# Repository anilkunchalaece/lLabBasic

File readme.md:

See the output at : 
http://pamda1ver2.16mb.com/index.html

refrences : 
https://developer.ibm.com/messaging/2013/05/22/program-messaging-apps-javascript/

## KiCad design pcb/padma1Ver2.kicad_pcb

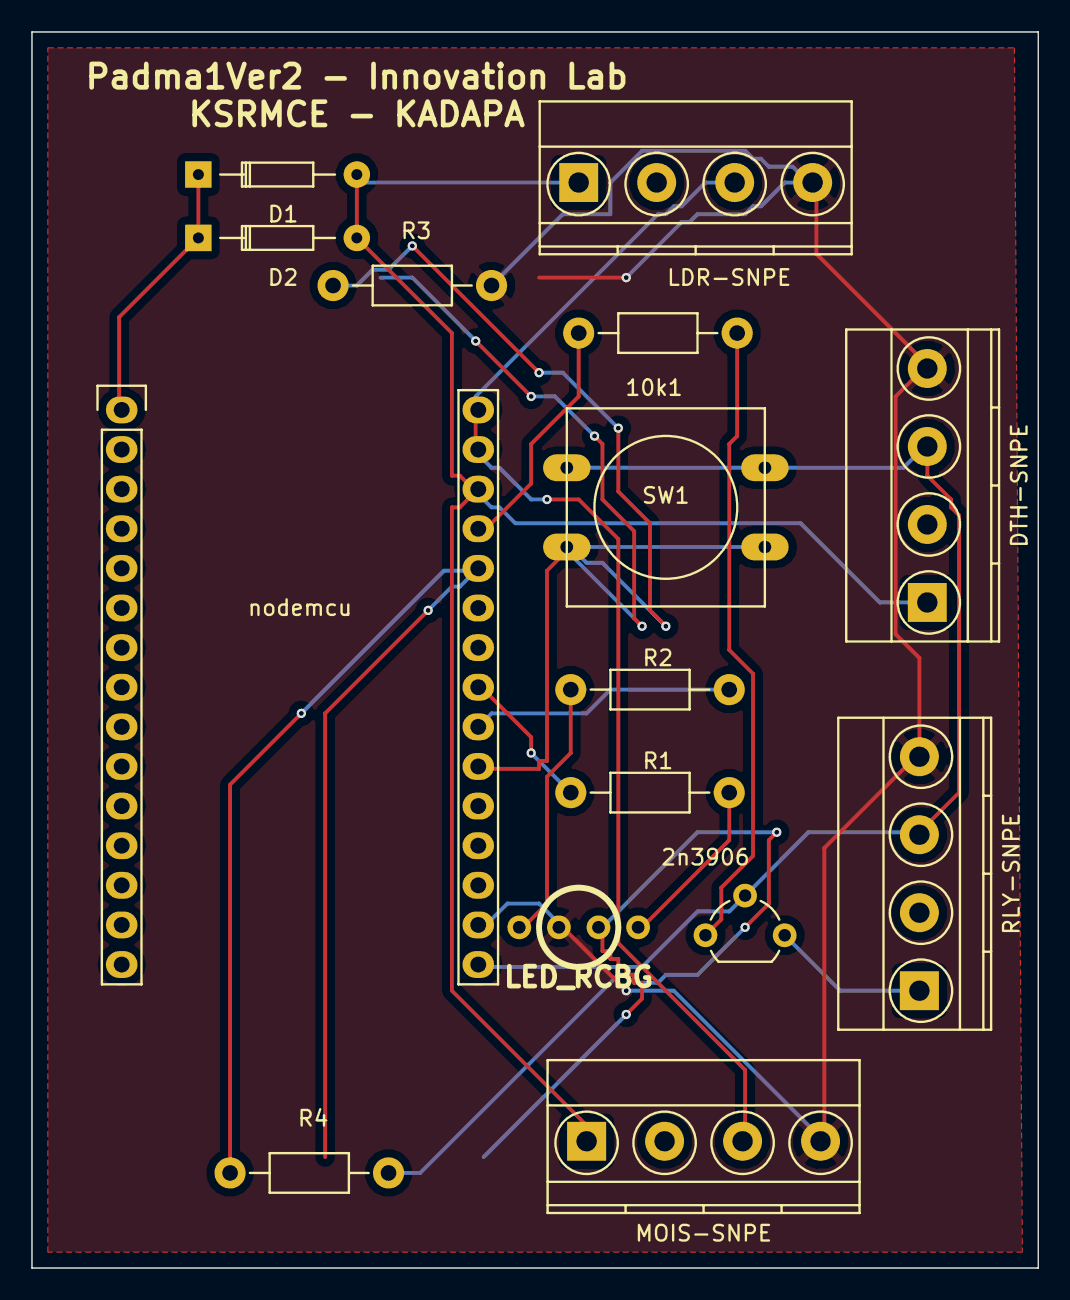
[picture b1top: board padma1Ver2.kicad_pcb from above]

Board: 2 copper layers, 64.5 x 79.2 mm, 15 parts (0 on the bottom side), 15 nets.

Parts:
2n3906: Q_PNP_BCE; TO-92_Molded_Wide
10k1: R; Resistor_Horizontal_RM10mm
D1, D2: D; Diode_DO-35_SOD27_Horizontal_RM10
D3: LED_RCBG; LED5_RGB_long_wide
DTH-SNPE: CONN_01X04; TerminalBlock_Pheonix_MKDS1.5-4pol
LDR-SNPE: CONN_01X04; TerminalBlock_Pheonix_MKDS1.5-4pol
MOIS-SNPE: CONN_01X04; TerminalBlock_Pheonix_MKDS1.5-4pol
R1, R2, R3, R4: R; Resistor_Horizontal_RM10mm
RLY-SNPE: RLY; TerminalBlock_Pheonix_MKDS1.5-4pol
SW1: SPST; SW_PUSH-12mm
nodemcu: nodemcu; NodeMCU_Amica_R2

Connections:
+3V3: 2n3906.2, DTH-SNPE.3, RLY-SNPE.3, SW1.1, nodemcu.16
/power: LDR-SNPE.3, MOIS-SNPE.3, nodemcu.29, nodemcu.30
/signal: D1.2, D2.2, DTH-SNPE.1, LDR-SNPE.1, MOIS-SNPE.1, nodemcu.28
Earth: D3.2, DTH-SNPE.4, LDR-SNPE.4, MOIS-SNPE.4, R3.2, RLY-SNPE.4, nodemcu.17
unnamed: 2n3906.3, RLY-SNPE.1
unnamed: 2n3906.1, 10k1.1
unnamed: 10k1.2, nodemcu.27
unnamed: D1.1, D2.1, nodemcu.1
unnamed: D3.1, R2.1
unnamed: D3.3, R4.2
unnamed: D3.4, R1.2
unnamed: R1.1, nodemcu.23
unnamed: R2.2, nodemcu.22
unnamed: R3.1, SW1.2, nodemcu.21
unnamed: R4.1, nodemcu.26

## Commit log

2016-09-13 Necessary Ingredients for Starting ESP8266 Project
2016-09-13 Working DTH sample code
2016-09-13 Added code to read moisture sensor value with Analog Input It Receives 3.3v max value so no need of voltage devider
2016-09-19 added Moisture and ldr sensor Code
2016-09-20 added wifi Connectivity
2016-09-20 added Http Post Request
2016-09-20 Echoing the post Request Data
2016-09-21 websitechanged tp Ksrmced.in
2016-09-21 database addition is Working
2016-09-21 to display values in Web
2016-09-30 added Bins with Json
2016-10-01 padma Config File
2016-10-01 configuration File for Padma1Ver2
2016-10-03 added sensorData and wifiConnectivity Files
2016-10-19 Fritzing File for Connections
2016-10-19 Connection Diagram
2016-11-03 Firmware Bin files including Json
2016-11-08 Working Rly control via MQTT and adafruit IO
2016-11-09 adafruitIO-pahoJS
2016-11-09 mqtt server file
2016-11-09 mqtt js file for server
2016-11-12 config File
2016-11-12 working File
2016-11-13 ws Vs wss
2016-11-13 Payload format for mqtt messages
2016-11-13 added useSSL for WSS
2016-11-13 added Device Id
2016-11-13 added MQTT parameters in deviceConfig File
2016-11-13 added mqttControl.lua and MQTT keywords added in config.json
2016-11-13 there is a syntax error in code mqttControl
2016-11-13 mqtt Control Bug Solved
2016-11-13 working code <for Now.. i think :)>
2016-11-13 global pMessage in mqttControl is Fixed
2016-11-13 replaced hardcoded values in mqttControl pMessage String
2016-11-13 added pcall to catch the cjson.decode Error
2016-11-14 removed front and ending brackets to avoid adafruitIO Errot
2016-11-14 added default duration to post sensor data and added genCompiledFiles.lua
2016-11-14 added init.lua file
2016-11-14 Working Code
2016-11-15 mqttSubscribe working files added with mqtt-js library
2016-11-15 solved Nill data bug
2016-11-15 added serverMode.lua and Modifed init.lua
2016-11-15 added simple access point code
2016-11-16 added fritzing file for PCB Design
2016-11-16 modifications for pcb
2016-11-16 basic schematic for padm1ver2
2016-11-16 schematic completed
2016-11-16 added layout
2016-11-16 with no electrical errors
2016-11-16 added WebApp files by Prof A Mohan
2016-11-16 WebApp Files added
2016-11-16 added nodemcu footprint
2016-11-17 added basic PCB
2016-11-17 added basic Pcb File
2016-11-17 added 3d Model
2016-11-17 added ConfigJson Description file
2016-11-17 solved a minor bug in deviceConfig file
2016-11-17 added No Pump Signa;
2016-11-18 added random clientid generator
2016-11-18 small bug in mqttControl Solved
2016-11-18 simple correction
2016-11-25 pcb Without Any Errors
2016-11-25 added pcb image
